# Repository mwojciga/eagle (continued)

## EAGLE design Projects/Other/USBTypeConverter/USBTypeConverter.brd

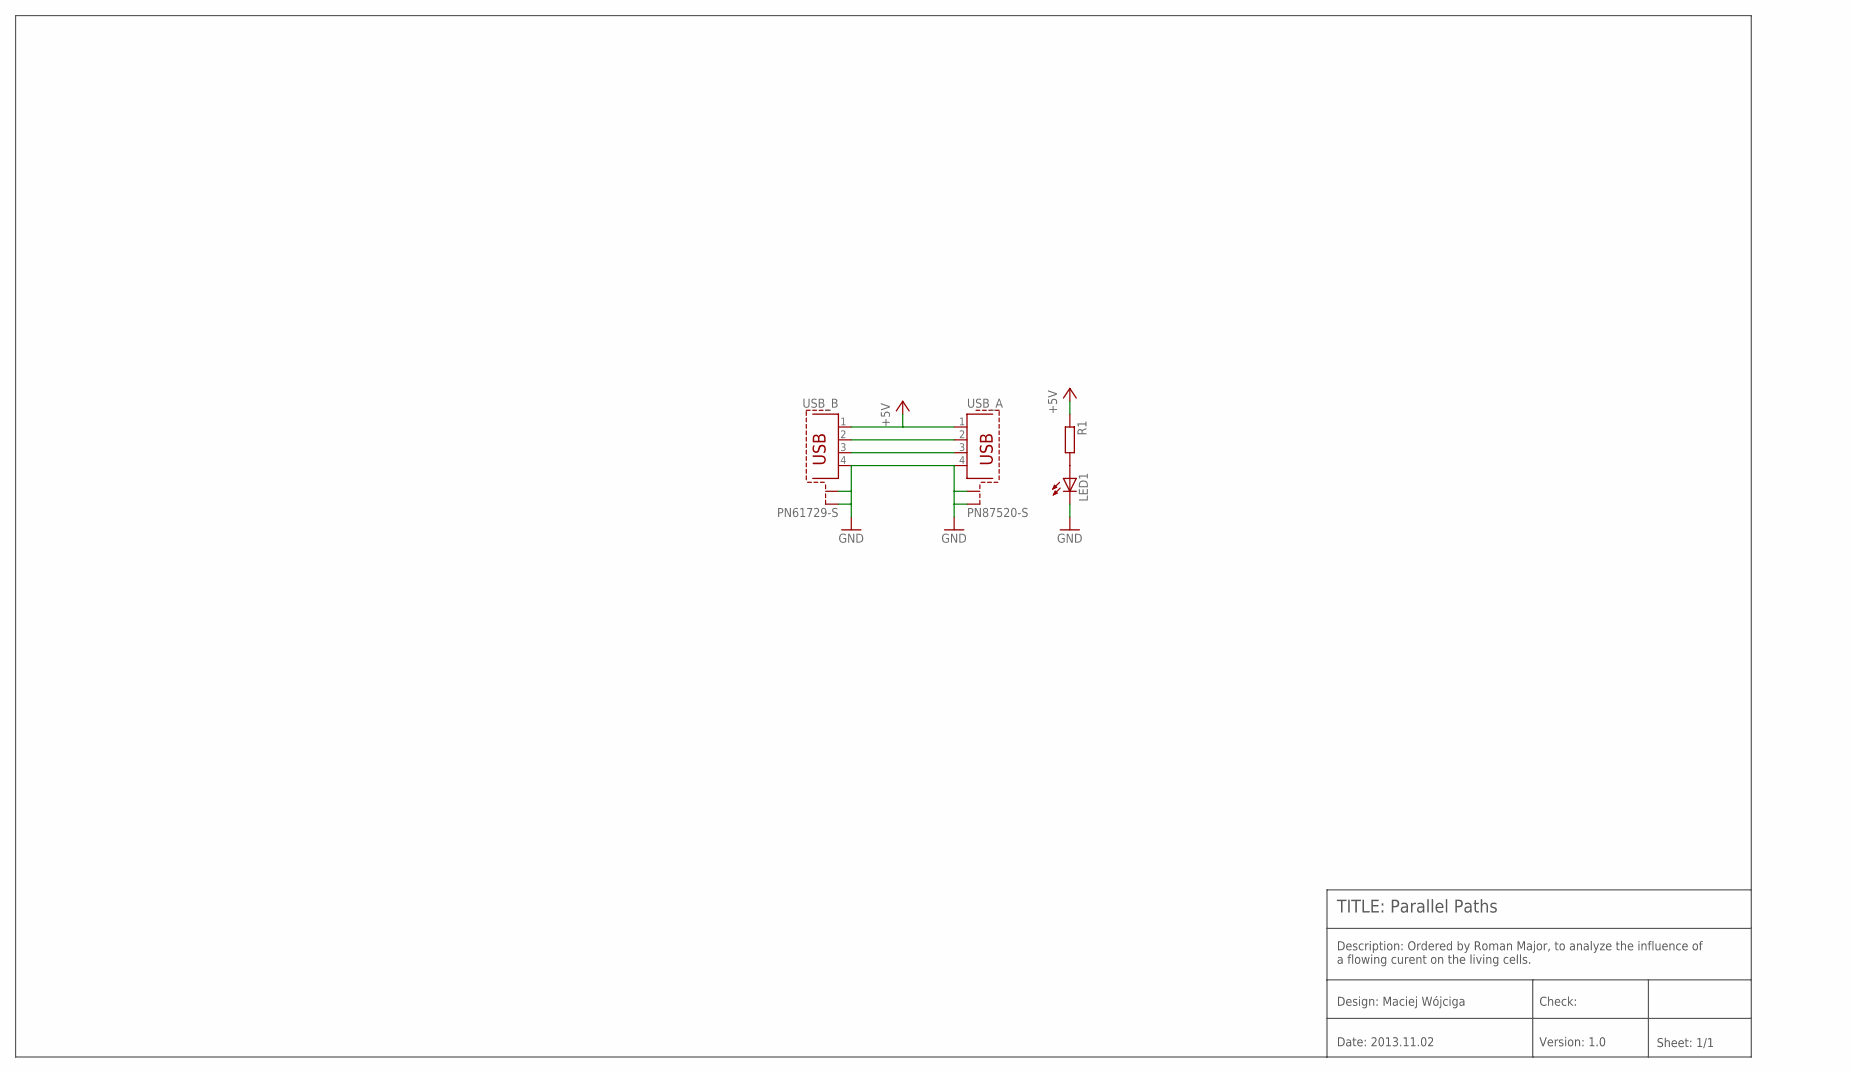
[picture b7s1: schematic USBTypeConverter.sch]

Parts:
LED1: LED3MM
R1: R-EU_0207/10; 0207/10
USB_A: PN87520-S
USB_B: PN61729-S

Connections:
+5V: R1.1, USB_A.1, USB_B.1
GND: LED1.K (C), USB_A.4, USB_A.S1, USB_A.S2, USB_B.4, USB_B.S1, USB_B.S2
unnamed: USB_A.2, USB_B.2
unnamed: USB_A.3, USB_B.3
unnamed: LED1.A, R1.2

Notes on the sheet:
TITLE: Parallel Paths
Design: Maciej Wójciga
Check:
Date: 2013.11.02
Version: 1.0
Sheet: 1/1
Description: Ordered by Roman Major, to analyze the influence of a flowing curent on the living cells.

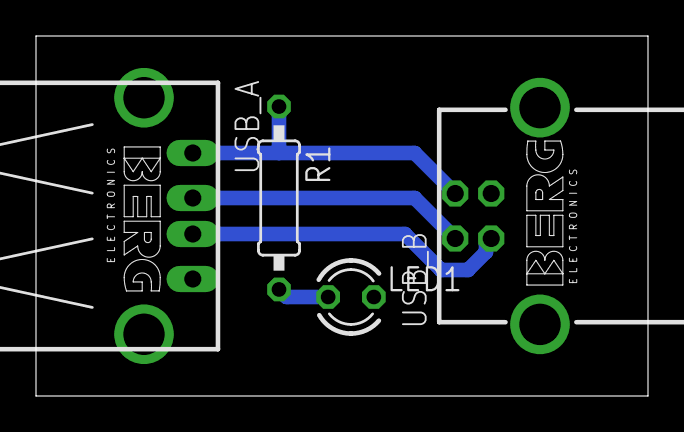
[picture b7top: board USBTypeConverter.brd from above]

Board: 2 copper layers, 34.0 x 20.0 mm, 4 parts (0 on the bottom side), 5 nets.

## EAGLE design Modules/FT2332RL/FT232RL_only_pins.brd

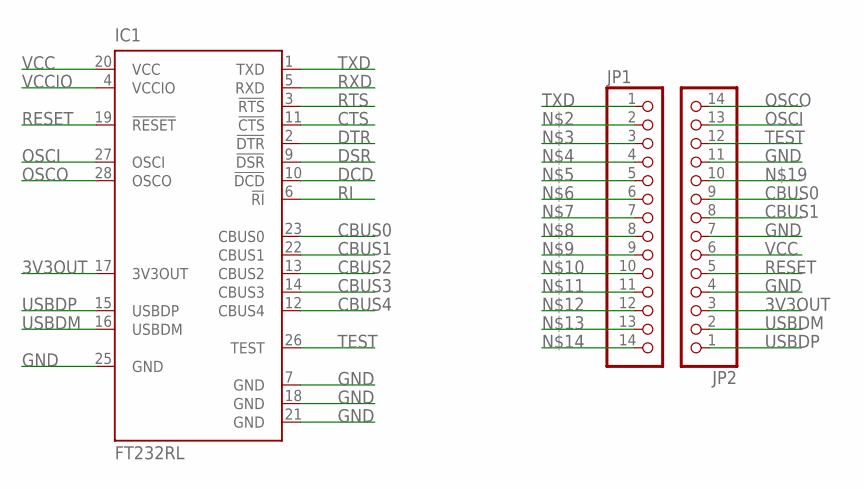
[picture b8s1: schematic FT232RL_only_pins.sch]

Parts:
IC1: FT232RL; SSOP28
JP1, JP2: PINHD-1X14; 1X14

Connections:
3V3OUT: IC1.17 (3V3OUT), JP2.3
CBUS0: IC1.23 (CBUS0), JP2.9
CBUS1: IC1.22 (CBUS1), JP2.8
CBUS2: IC1.13 (CBUS2)
CBUS3: IC1.14 (CBUS3)
CBUS4: IC1.12 (CBUS4)
CTS: IC1.11 (!CTS)
DCD: IC1.10 (!DCD)
DSR: IC1.9 (!DSR)
DTR: IC1.2 (!DTR)
GND: IC1.7 (GND), IC1.18 (GND), IC1.21 (GND), IC1.25 (GND), JP2.4, JP2.7, JP2.11
OSCI: IC1.27 (OSCI), JP2.13
OSCO: IC1.28 (OSCO), JP2.14
RESET: IC1.19 (!RESET), JP2.5
RI: IC1.6 (!RI)
RTS: IC1.3 (!RTS)
RXD: IC1.5 (RXD)
TEST: IC1.26 (TEST), JP2.12
TXD: IC1.1 (TXD), JP1.1
USBDM: IC1.16 (USBDM), JP2.2
USBDP: IC1.15 (USBDP), JP2.1
VCC: IC1.20 (VCC), JP2.6
VCCIO: IC1.4 (VCCIO)

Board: 2 copper layers, 3 parts (0 on the bottom side), 12 nets, no tracks yet.

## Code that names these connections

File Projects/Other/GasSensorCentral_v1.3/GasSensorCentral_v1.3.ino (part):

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20160306: Code copied from GasSensorModule_v1.00

SENSOR PINS:
PB2: DHT
PD6: PIR
A0: LIGHT
A1: GAS

BUTTON PINS:
PD2: BUTTON1
PD3: BUTTON2
PD4: BUTTON3
PD5: BUTTON4

LED PINS:
A0: LED1
A2: LED2
PD6: LED3
PB2: LED4 - digital pin 10

TODO:
If button pressed, send SMS with the module code and pressed button number. Appropriate LED starts to blink.
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dht DHT11;

// Define constraints.
#define BUTTON1 2
#define BUTTON2 3
#define BUTTON3 4
#define BUTTON4 5

#define LED1 A0
#define LED2 A2
#define LED3 6
#define LED4 10

#define DHT 10
#define PIR 6
#define LIGHT A0
#define GAS A1

// Define global variables.
boolean button1State;
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void setup() {
  //GPRS.begin(19200); // In v2.4 board version, we communicate using RXTX ports, not Software Serial.
  Serial.begin(19200);
  pinMode(BUTTON1, INPUT);
  pinMode(BUTTON2, INPUT);
  pinMode(BUTTON3, INPUT);
  pinMode(BUTTON4, INPUT);
  pinMode(LED1, OUTPUT);
  pinMode(LED2, OUTPUT);
  pinMode(LED3, OUTPUT);
  pinMode(LED4, OUTPUT);
  printf_begin();
  /*// Radio.
  printf_begin(); // It must be here!
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
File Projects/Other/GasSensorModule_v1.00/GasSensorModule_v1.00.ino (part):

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1. Change thresholds methods, change minGZ, change maxGZ, etc.
 
SENSOR PINS:
PC0: GAS
PC1: TEMP
PC2: LIGHT
PC3: DHT
PD2: MOTION
PD3: LED1
PD4: BUTTON1
PD7: CSN
PB0: CE
PB3: MOSI
PB4: MISO
PB5: SCK

Notes:
Max 32 characters can be sent at one time.
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  // TEMPERATURE.
  //dataOT = analogRead(pinOT);
  //dataOT = dataOT * 0.48828125;
  int chk = DHT.read11(pinHO);
  dataOT = DHT.temperature,1;
}

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void getHO() {
  // HUMIDITY.
  //Serial.print("DHT11, ");
  int chk = DHT.read11(pinHO);
  /*switch (chk)
  {
    case DHTLIB_OK:  
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
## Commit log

2022-07-14 Migrate to GitHub
2022-07-17 Migrate Biorobot related projects to a different repo.
